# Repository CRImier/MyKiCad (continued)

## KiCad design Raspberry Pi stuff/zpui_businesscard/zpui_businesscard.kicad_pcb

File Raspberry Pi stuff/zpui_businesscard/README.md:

# ZPUI businesscard

## Are you here from the link on the businesscard?

The assembly should be pretty easy - as long as you have 8 buttons of the simplest kind, an generic 4-pin I2C OLED screen,
and a pin header to connect this to a Pi, it should work wonders. It's designed to work with [ZPUI](https://zpui.readthedocs.io/en/latest/)!

### Update 04.02.25

ZPUI has been polished back up to function. Docs on the businesscard software setup are in progress!

Any questions? Join [#zerophone:matrix.org](https://github.com/CRImier/MyKiCad/tree/master/Raspberry%20Pi%20stuff/zpui_businesscard) on Matrix, or [message me](https://linktr.ee/CRImier) for setup/assembly help!

## Images

## Info

- Software: Kicad 8
- Version: 1
- PCB size: 89x51mm
- Layer count: 2
- Recommended thickness: 0.8mm-1mm (I manufactured 1mm and it was fine)

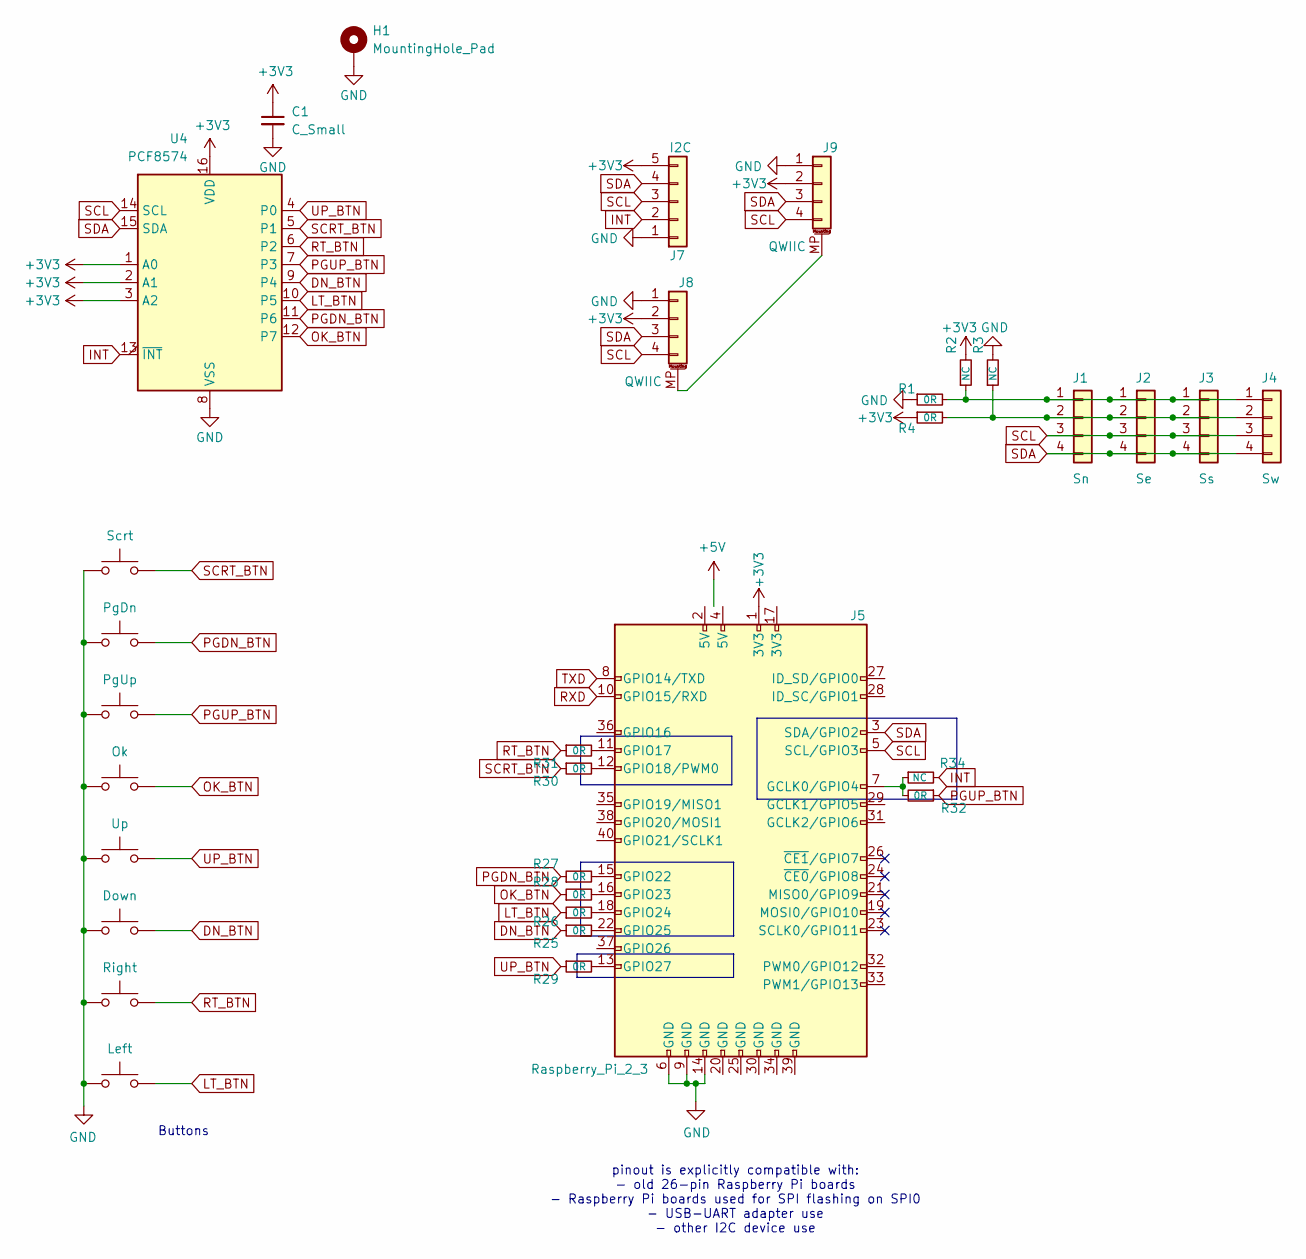
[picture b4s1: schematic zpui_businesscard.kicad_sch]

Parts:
C1: C_Small; C_0603_1608Metric
H1: MountingHole_Pad; MountingHole_3mm_Pad
J1: Sn; PinHeader_1x04_P2.54mm_Vertical
J2: Se; PinHeader_1x04_P2.54mm_Vertical
J3: Ss; PinHeader_1x04_P2.54mm_Vertical
J4: Sw; PinHeader_1x04_P2.54mm_Vertical
J5: Raspberry_Pi_2_3; RASPBERRY_PI_HAT
J7: I2C; PinHeader_1x05_P2.54mm_Vertical
J8, J9: QWIIC; JST_SH_SM04B-SRSS-TB_1x04-1MP_P1.00mm_Horizontal
R1, R4, R25, R26, R27, R28, R29, R30, R31, R32: 0R; R_0603_1608Metric_Jumper
R2, R3, R34: NC; R_0603_1608Metric
SW1: PgDn; SW_SPST_PTS645; LCSC Part # C285456
SW2: Scrt; SW_SPST_PTS645; LCSC Part # C285456
SW7: PgUp; SW_SPST_PTS645; LCSC Part # C285456
SW8: Ok; SW_SPST_PTS645; mpn REQUIRED https://www.lcsc.com/product-d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; LCSC Part # C285456
SW9: Up; SW_SPST_PTS645; mpn REQUIRED https://www.lcsc.com/product-d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; LCSC Part # C285456
SW10: Down; SW_SPST_PTS645; mpn REQUIRED https://www.lcsc.com/product-d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; LCSC Part # C285456
SW11: Right; SW_SPST_PTS645; mpn REQUIRED https://www.lcsc.com/product-d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; LCSC Part # C285456
SW12: Left; SW_SPST_PTS645; mpn REQUIRED https://www.lcsc.com/product-d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; LCSC Part # C285456
U4: PCF8574; SOIC-16W_7.5x10.3mm_P1.27mm

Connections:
+3V3: C1.1, J5.1 (3V3), J7.5, J8.2, J9.2, R2.2, R4.1, U4.1 (A0), U4.2 (A1), U4.3 (A2), U4.16 (VDD)
DN_BTN: R25.1, SW10.1, U4.9 (P4)
GND: C1.2, H1.1, J5.6 (GND), J5.9 (GND), J5.14 (GND), J7.1, J8.1, J9.1, R1.1, R3.2, SW1.2, SW2.2, SW7.2, SW8.2, SW9.2, SW10.2, SW11.2, SW12.2, U4.8 (VSS)
INT: J7.2, R34.2, U4.13 (~INT)
LT_BTN: R26.1, SW12.1, U4.10 (P5)
unnamed: J1.1, J2.1, J3.1, J4.1, R1.2, R2.1
unnamed: J1.2, J2.2, J3.2, J4.2, R3.1, R4.2
unnamed: J5.7 (GCLK0/GPIO4), R32.2, R34.1
unnamed: J5.11 (GPIO17), R31.2
unnamed: J5.12 (GPIO18/PWM0), R30.2
unnamed: J5.15 (GPIO22), R27.2
unnamed: J5.16 (GPIO23), R28.2
unnamed: J5.18 (GPIO24), R26.2
unnamed: J5.22 (GPIO25), R25.2
unnamed: J5.13 (GPIO27), R29.2
unnamed: J8.MP (MountPin), J9.MP (MountPin)
OK_BTN: R28.1, SW8.1, U4.12 (P7)
PGDN_BTN: R27.1, SW1.1, U4.11 (P6)
PGUP_BTN: R32.1, SW7.1, U4.7 (P3)
RT_BTN: R31.1, SW11.1, U4.6 (P2)
RXD: J5.10 (GPIO15/RXD)
SCL: J1.3, J2.3, J3.3, J4.3, J5.5 (SCL/GPIO3), J7.3, J8.4, J9.4, U4.14 (SCL)
SCRT_BTN: R30.1, SW2.1, U4.5 (P1)
SDA: J1.4, J2.4, J3.4, J4.4, J5.3 (SDA/GPIO2), J7.4, J8.3, J9.3, U4.15 (SDA)
TXD: J5.8 (GPIO14/TXD)
UP_BTN: R29.1, SW9.1, U4.4 (P0)

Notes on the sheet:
Buttons
pinout is explicitly compatible with: - old 26-pin Raspberry Pi boards - Raspberry Pi boards used for SPI flashing on SPI0 - USB-UART adapter use - other I2C device use

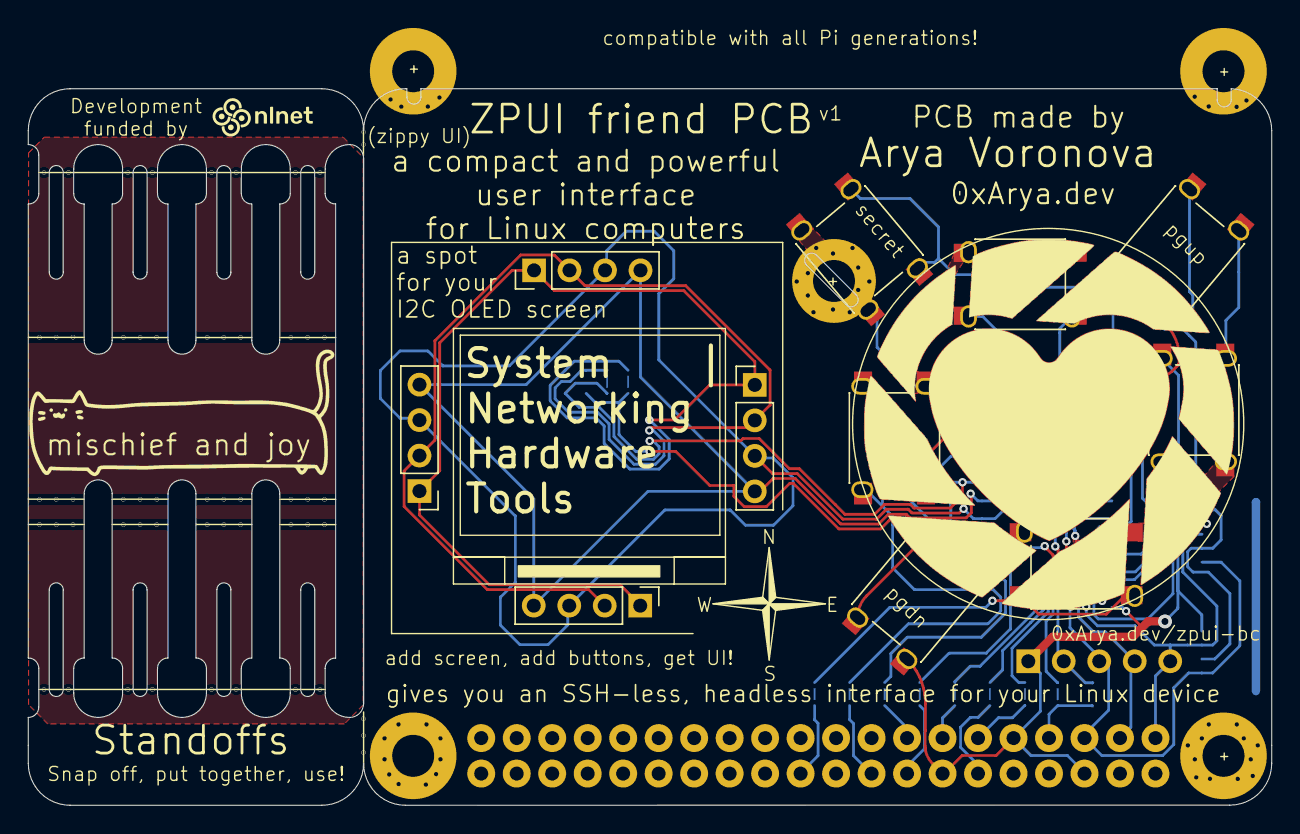
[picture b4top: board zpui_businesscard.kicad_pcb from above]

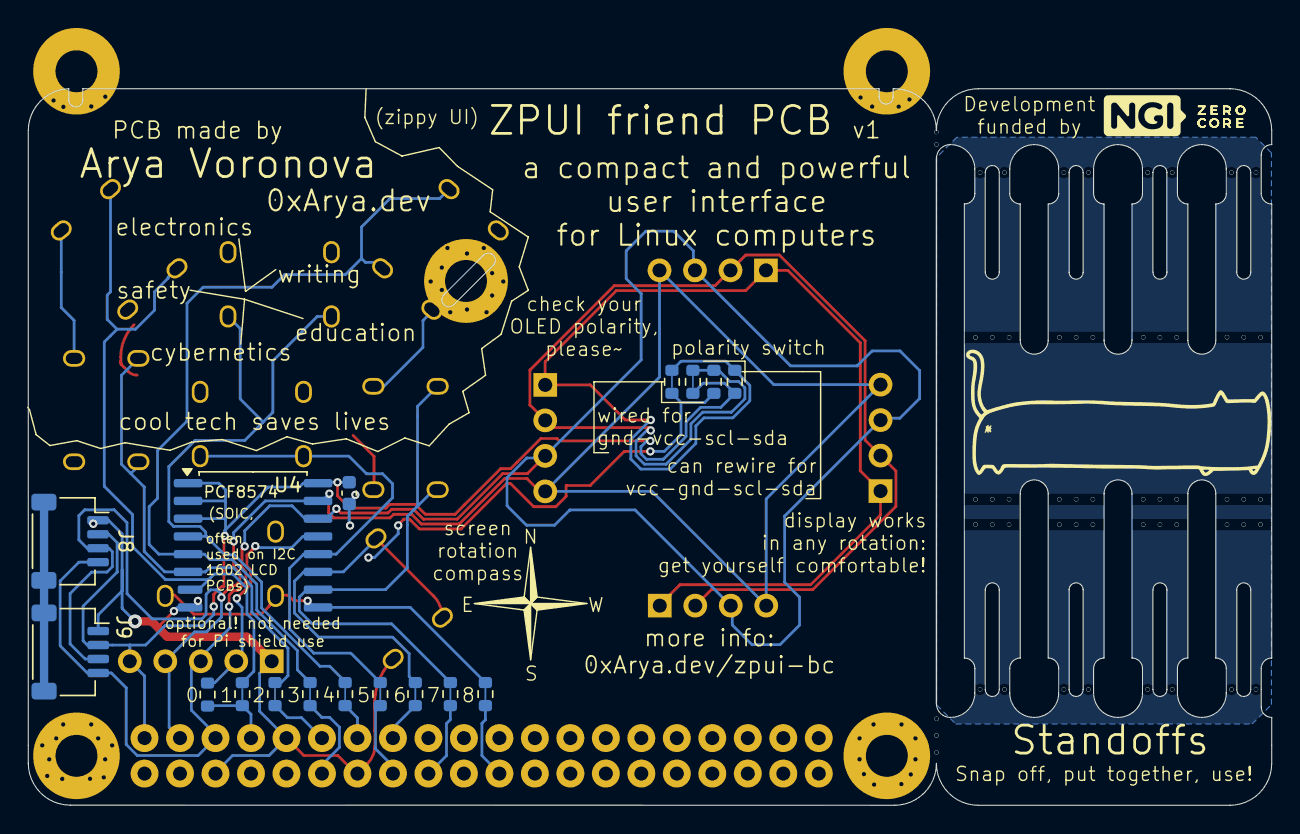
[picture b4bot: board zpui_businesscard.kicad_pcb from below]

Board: 2 copper layers, 89.0 x 51.3 mm, 32 parts (17 on the bottom side), 24 nets.

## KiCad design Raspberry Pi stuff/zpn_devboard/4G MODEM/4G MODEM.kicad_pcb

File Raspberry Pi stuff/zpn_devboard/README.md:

# ZPN devboard

work in progress :3

## Images

## Notes

- This board is untested and there's no guarantees of fitness.
- I recommend a stencil for assembling this board.

## Info

- Software: Kicad 8
- Version: 0
- PCB size: 100x100
- Layer count: 2
- Recommended thickness: 1.6mm

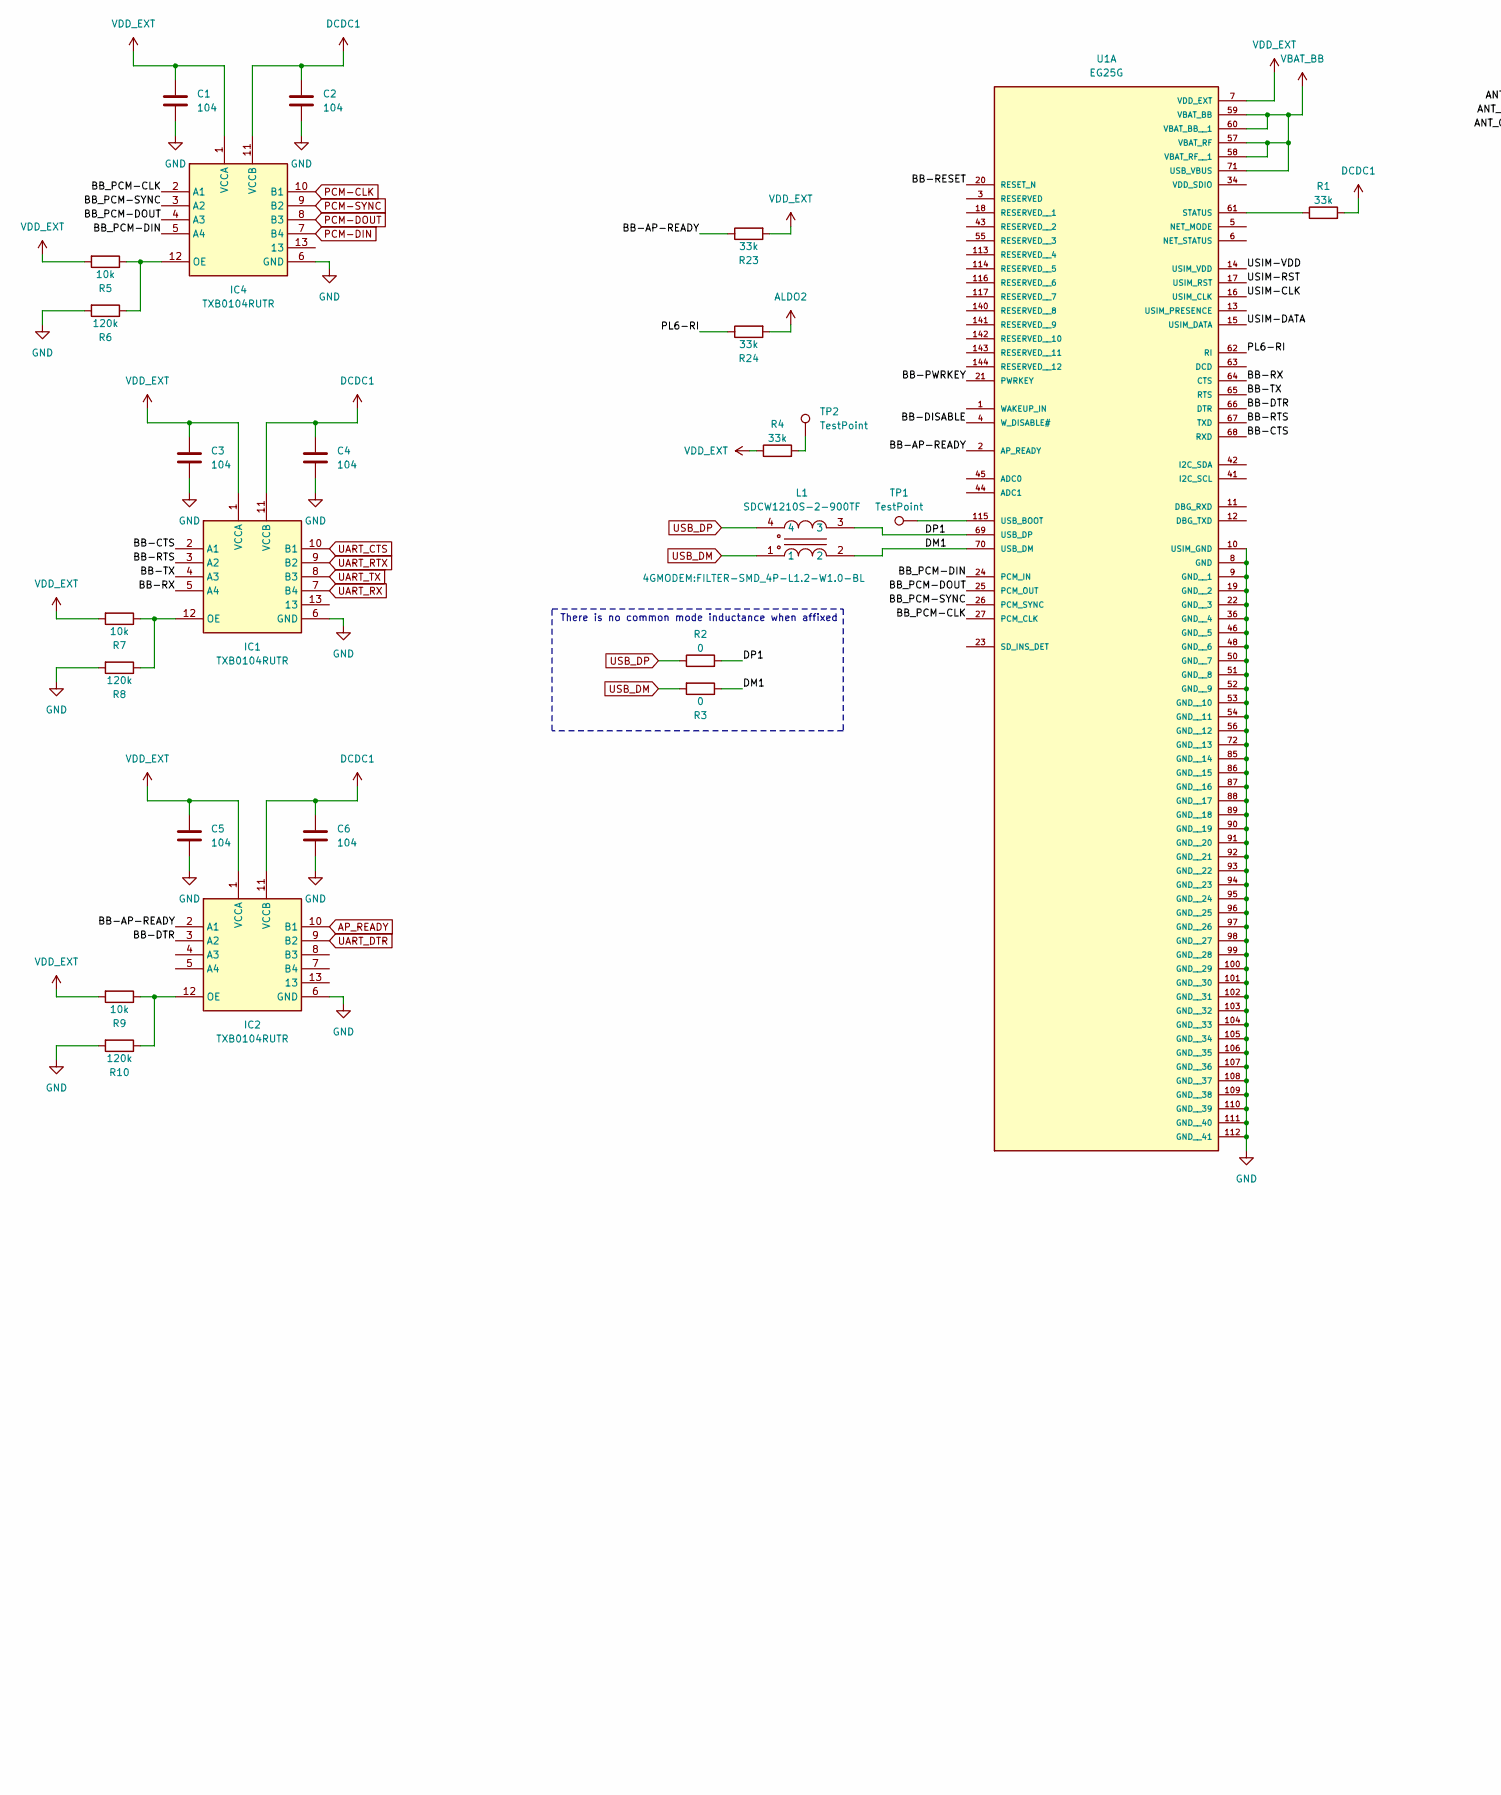
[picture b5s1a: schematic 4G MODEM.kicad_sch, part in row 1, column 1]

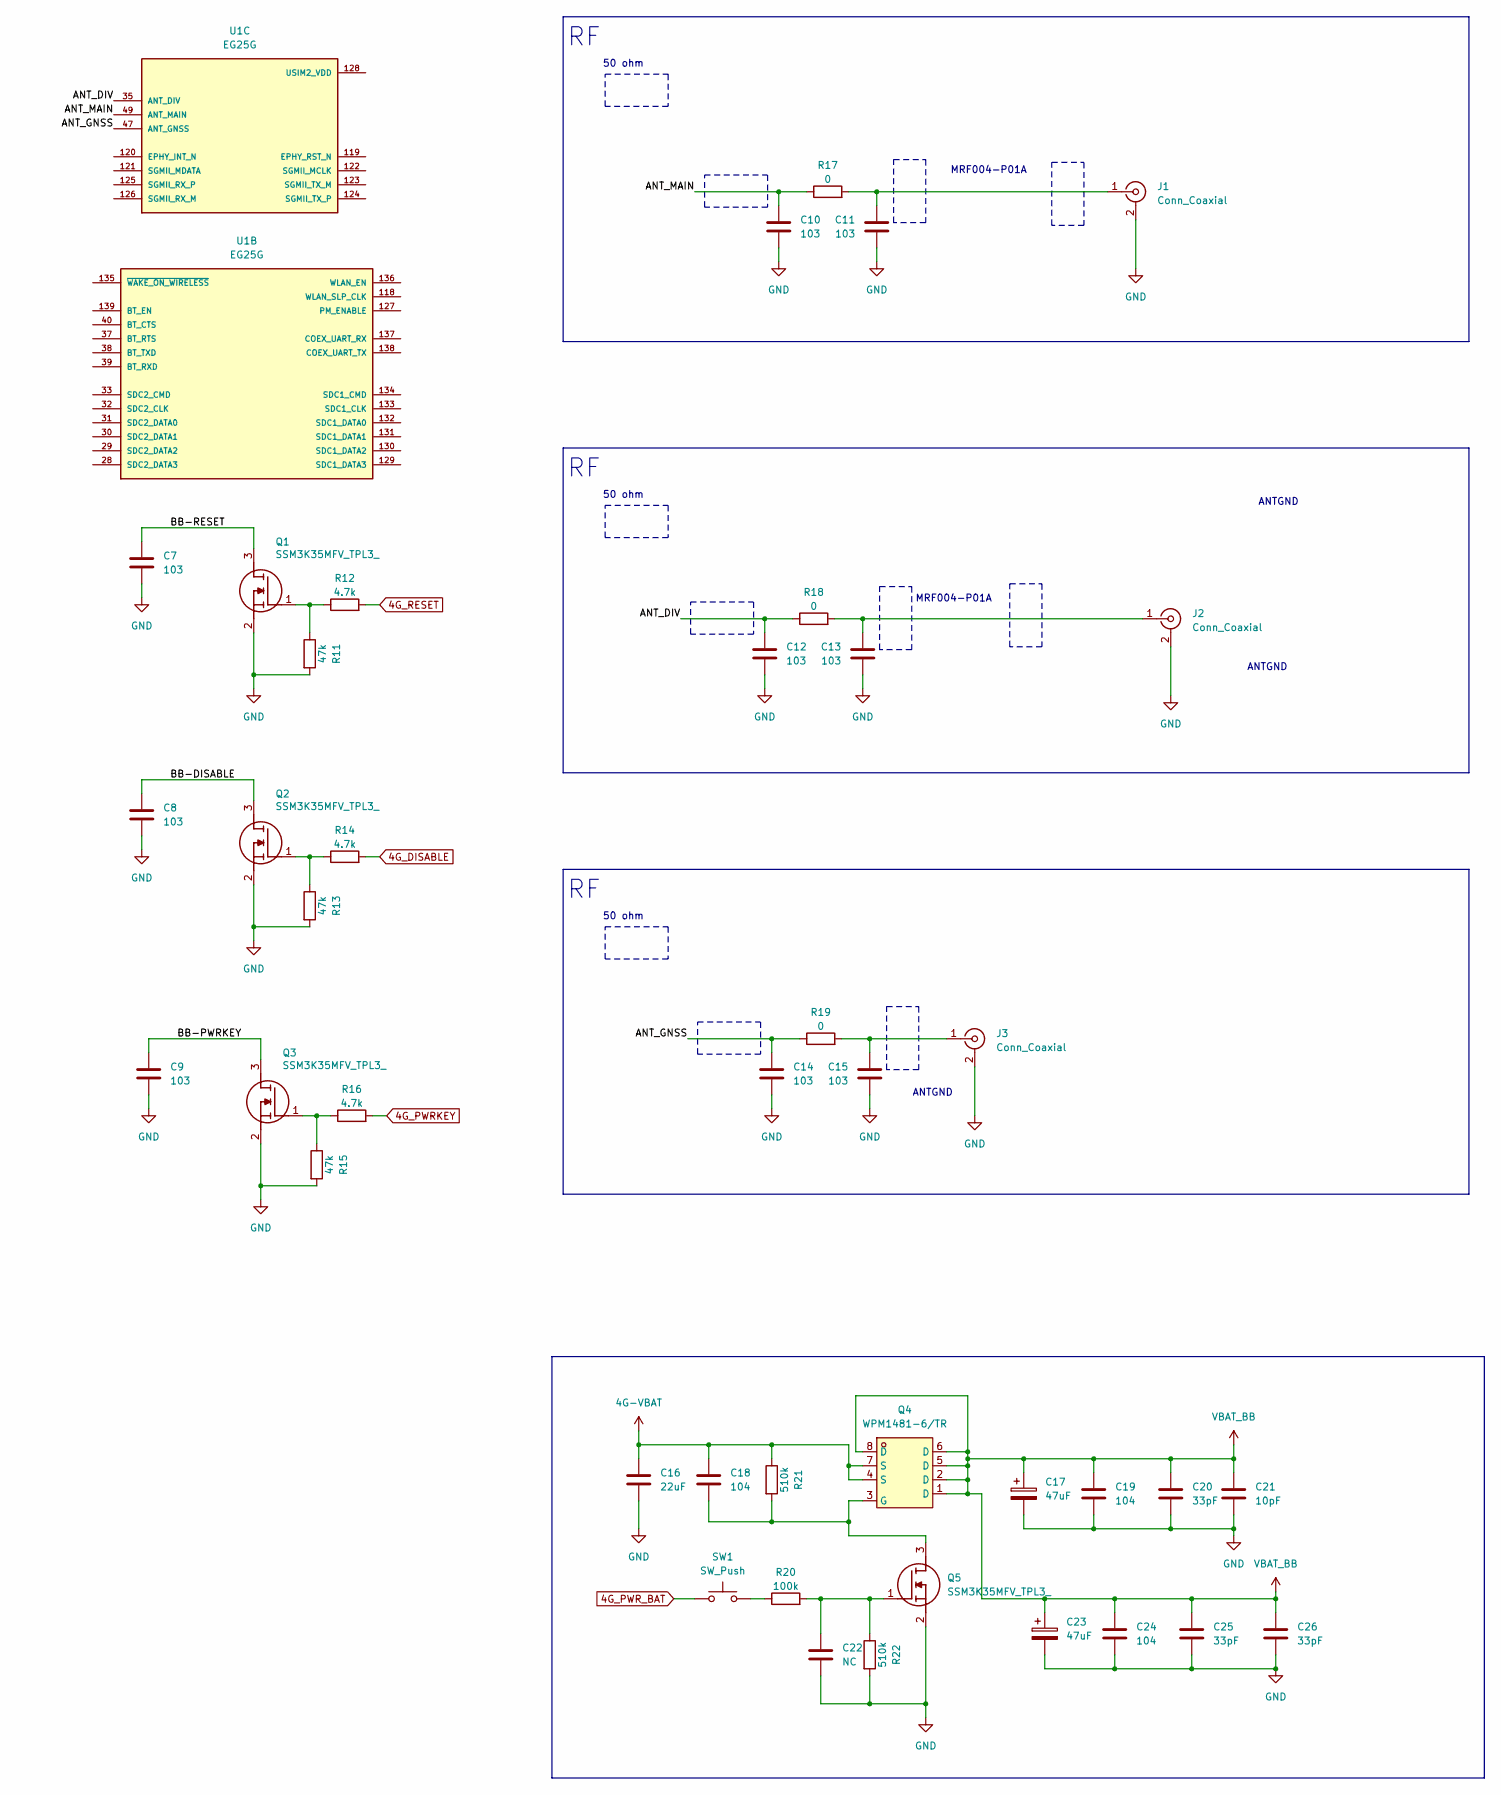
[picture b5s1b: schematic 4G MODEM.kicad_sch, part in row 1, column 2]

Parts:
C1, C2, C3, C4, C5, C6, C18, C19, C24: 104; C_0402_1005Metric
C7, C8, C9, C10, C11, C12, C13, C14, C15: 103; C_0402_1005Metric
C16: 22uF; C_0402_1005Metric
C17, C23: 47uF; C_0402_1005Metric
C20, C25, C26: 33pF; C_0402_1005Metric
C21: 10pF; C_0402_1005Metric
C22: NC; C_0402_1005Metric
IC1, IC2, IC4: TXB0104RUTR; Mouser Part Number 595-TXB0104RUTR
J1, J2, J3: Conn_Coaxial; U.FL_Molex_MCRF_73412-0110_Vertical
L1: SDCW1210S-2-900TF; FILTER-SMD_4P-L1.2-W1.0-BL; LCSC Part C370242
Q1, Q2, Q3, Q5: SSM3K35MFV_TPL3_; SOTFL40P120X55-3N; Mouser Part Number 757-SSM3K35MFVTPL3
Q4: WPM1481-6/TR; DFN-6L_L2.0-W2.0-P0.65-BL_WPM1481-6; LCSC Part C239798
R1, R4, R23, R24: 33k; R_0402_1005Metric
R2, R3, R17, R18, R19: 0; R_0402_1005Metric
R5, R7, R9: 10k; R_0402_1005Metric
R6, R8, R10: 120k; R_0402_1005Metric
R11, R13, R15: 47k; R_0402_1005Metric
R12, R14, R16: 4.7k; R_0402_1005Metric
R20: 100k; R_0402_1005Metric
R21, R22: 510k; R_0402_1005Metric
SW1: SW_Push; SW_PUSH_6mm
TP1, TP2: TestPoint; TestPoint_Pad_D2.0mm
U1: EG25G; XCVR_EG25G; PARTREV 1.2

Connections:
4G-VBAT: C16.1, C18.1, Q4.4 (S), Q4.7 (S), R21.1
4G_DISABLE: R14.2
4G_PWRKEY: R16.2
4G_PWR_BAT: SW1.1
4G_RESET: R12.2
/ANT_DIV: C12.1, R18.1, U1.35 (ANT_DIV)
/ANT_GNSS: C14.1, R19.1, U1.47 (ANT_GNSS)
/ANT_MAIN: C10.1, R17.1, U1.49 (ANT_MAIN)
/BB-AP-READY: IC2.2 (A1), R23.1, U1.2 (AP_READY)
/BB-CTS: IC1.2 (A1), U1.68 (RXD)
/BB-DISABLE: C8.1, Q2.3 (D), U1.4 (W_DISABLE#)
/BB-DTR: IC2.3 (A2), U1.66 (DTR)
/BB-PWRKEY: C9.1, Q3.3 (D), U1.21 (PWRKEY)
/BB-RESET: C7.1, Q1.3 (D), U1.20 (RESET_N)
/BB-RTS: IC1.3 (A2), U1.67 (TXD)
/BB-RX: IC1.5 (A4), U1.64 (CTS)
/BB-TX: IC1.4 (A3), U1.65 (RTS)
/BB_PCM-CLK: IC4.2 (A1), U1.27 (PCM_CLK)
/BB_PCM-DIN: IC4.5 (A4), U1.24 (PCM_IN)
/BB_PCM-DOUT: IC4.4 (A3), U1.25 (PCM_OUT)
/BB_PCM-SYNC: IC4.3 (A2), U1.26 (PCM_SYNC)
/DM1: L1.2, R3.1, U1.70 (USB_DM)
/DP1: L1.3, R2.2, U1.69 (USB_DP)
/PL6-RI: R24.1, U1.62 (RI)
/USIM-CLK: U1.16 (USIM_CLK)
/USIM-DATA: U1.15 (USIM_DATA)
/USIM-RST: U1.17 (USIM_RST)
/USIM-VDD: U1.14 (USIM_VDD)
ALDO2: R24.2
AP_READY: IC2.10 (B1)
DCDC1: C2.1, C4.1, C6.1, IC1.11 (VCCB), IC2.11 (VCCB), IC4.11 (VCCB), R1.2
GND: C1.2, C2.2, C3.2, C4.2, C5.2, C6.2, C7.2, C8.2, C9.2, C10.2, C11.2, C12.2, C13.2, C14.2, C15.2, C16.2, C17.2, C19.2, C20.2, C21.2, C22.2, C23.2, C24.2, C25.2, C26.2, IC1.6 (GND), IC2.6 (GND), IC4.6 (GND), J1.2 (Ext), J2.2 (Ext), J3.2 (Ext), Q1.2 (S), Q2.2 (S), Q3.2 (S), Q5.2 (S), R6.2, R8.2, R10.2, R11.2, R13.2, R15.2, R22.2, U1.8 (GND), U1.9 (GND__1), U1.10 (USIM_GND), U1.19 (GND__2), U1.22 (GND__3), U1.36 (GND__4), U1.46 (GND__5), U1.48 (GND__6), U1.50 (GND__7), U1.51 (GND__8), U1.52 (GND__9), U1.53 (GND__10), U1.54 (GND__11), U1.56 (GND__12), U1.72 (GND__13), U1.85 (GND__14), U1.86 (GND__15), U1.87 (GND__16), U1.88 (GND__17), U1.89 (GND__18), U1.90 (GND__19), U1.91 (GND__20), U1.92 (GND__21), U1.93 (GND__22), U1.94 (GND__23), U1.95 (GND__24), U1.96 (GND__25), U1.97 (GND__26), U1.98 (GND__27), U1.99 (GND__28), U1.100 (GND__29), U1.101 (GND__30), U1.102 (GND__31), U1.103 (GND__32), U1.104 (GND__33), U1.105 (GND__34), U1.106 (GND__35), U1.107 (GND__36), U1.108 (GND__37), U1.109 (GND__38), U1.110 (GND__39), U1.111 (GND__40), U1.112 (GND__41)
unnamed: IC1.12 (OE), R7.1, R8.1
unnamed: IC2.12 (OE), R9.1, R10.1
unnamed: IC4.12 (OE), R5.1, R6.1
unnamed: C11.1, J1.1 (In), R17.2
unnamed: C13.1, J2.1 (In), R18.2
unnamed: C15.1, J3.1 (In), R19.2
unnamed: Q1.1 (G), R11.1, R12.1
unnamed: Q2.1 (G), R13.1, R14.1
unnamed: Q3.1 (G), R15.1, R16.1
unnamed: C18.2, Q4.3 (G), Q5.3 (D), R21.2
unnamed: C22.1, Q5.1 (G), R20.2, R22.1
unnamed: R4.2, TP2.1
unnamed: R20.1, SW1.2
unnamed: R1.1, U1.61 (STATUS)
unnamed: TP1.1, U1.115 (USB_BOOT)
PCM-CLK: IC4.10 (B1)
PCM-DIN: IC4.7 (B4)
PCM-DOUT: IC4.8 (B3)
PCM-SYNC: IC4.9 (B2)
UART_CTS: IC1.10 (B1)
UART_DTR: IC2.9 (B2)
UART_RTX: IC1.9 (B2)
UART_RX: IC1.7 (B4)
UART_TX: IC1.8 (B3)
USB_DM: L1.1, R3.2
USB_DP: L1.4, R2.1
VBAT_BB: C17.1, C19.1, C20.1, C21.1, C23.1, C24.1, C25.1, C26.1, Q4.1 (D), Q4.2 (D), Q4.5 (D), Q4.6 (D), Q4.8 (D), U1.57 (VBAT_RF), U1.58 (VBAT_RF__1), U1.59 (VBAT_BB), U1.60 (VBAT_BB__1), U1.71 (USB_VBUS)
VDD_EXT: C1.1, C3.1, C5.1, IC1.1 (VCCA), IC2.1 (VCCA), IC4.1 (VCCA), R4.1, R5.2, R7.2, R9.2, R23.2, U1.7 (VDD_EXT)

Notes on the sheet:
50 ohm
There is no common mode inductance when affixed
MRF004-P01A
ANTGND

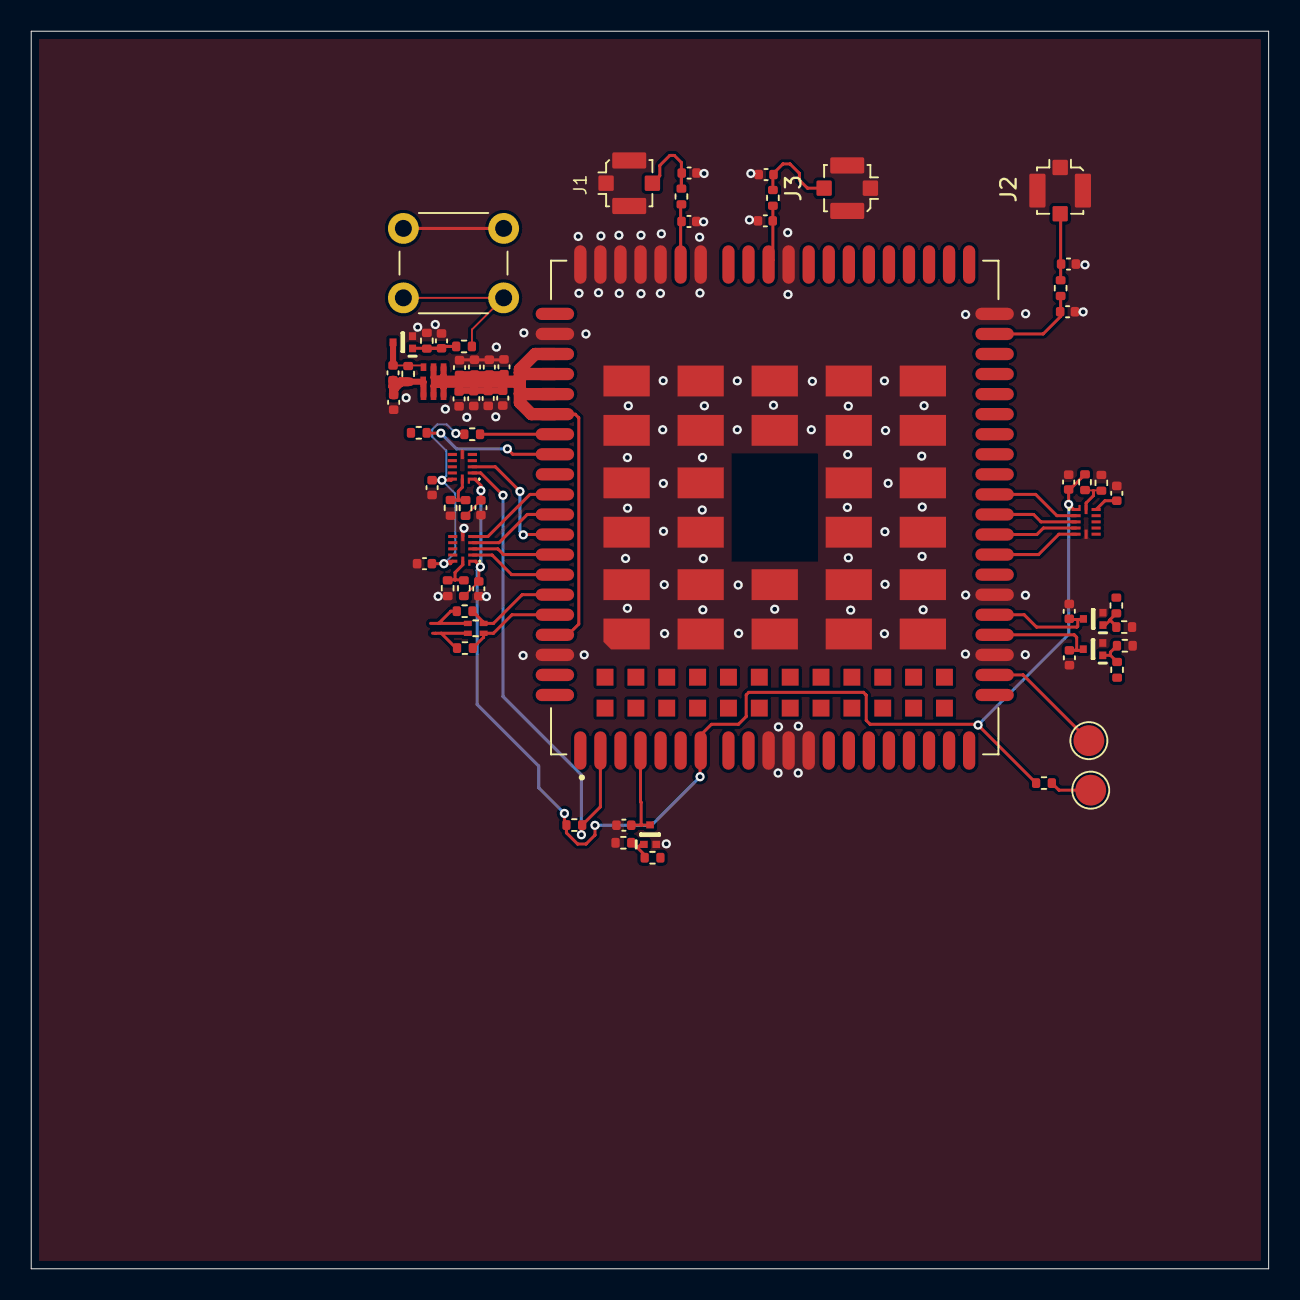
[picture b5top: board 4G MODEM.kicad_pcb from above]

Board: 4 copper layers, 80.2 x 80.2 mm, 66 parts (0 on the bottom side), 41 nets.
